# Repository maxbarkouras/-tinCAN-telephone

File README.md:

# tinCAN-telephone
Remotely send and receive CAN messages over WiFi.

**Hardware Requirements:**
- ESP32 (TWAI enabled)
- CAN Transceiver
  
**For OBD connections, you must also include:**
  - Buck Converter (minimum 12V at 1A)
  - OBD2 Cable

Wiring example using ESP32 Wroom, SN65HVD230, and LM2596:

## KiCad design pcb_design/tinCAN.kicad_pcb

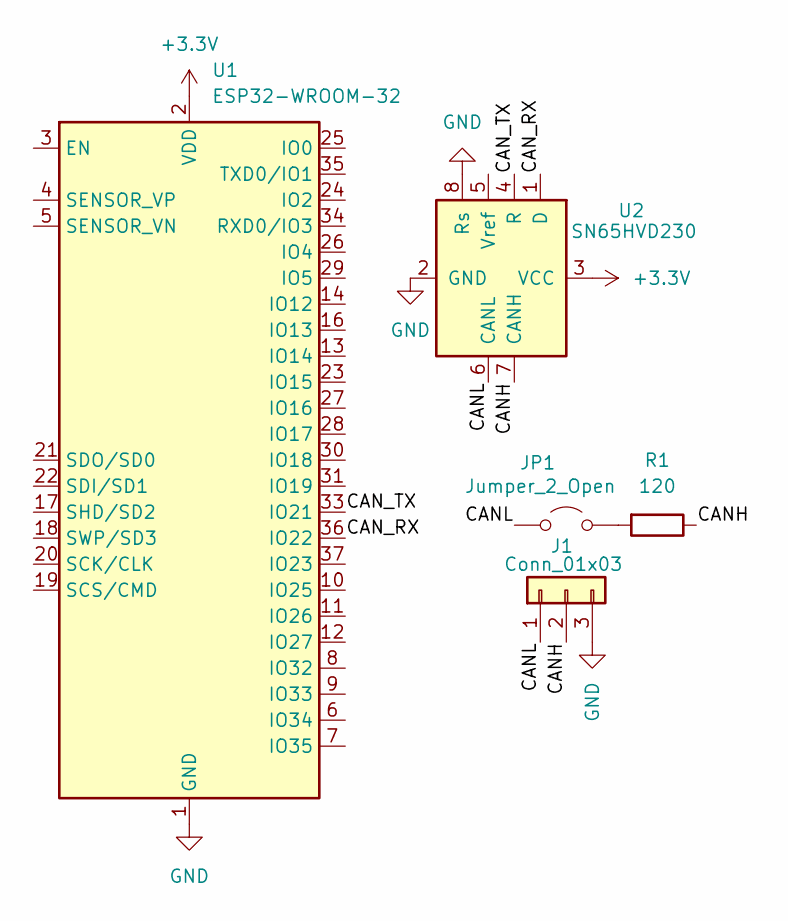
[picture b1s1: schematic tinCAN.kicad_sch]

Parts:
J1: Conn_01x03; PinSocket_1x03_P2.54mm_Vertical
JP1: Jumper_2_Open; PinSocket_1x02_P2.54mm_Vertical
R1: 120; R_0201_0603Metric
U1: ESP32-WROOM-32
U2: SN65HVD230; SOIC-8_3.9x4.9mm_P1.27mm

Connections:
+3.3V: U1.2 (VDD), U2.3 (VCC)
/CANH: J1.2, R1.1, U2.7 (CANH)
/CANL: J1.1, JP1.1 (A), U2.6 (CANL)
/CAN_RX: U1.36 (IO22), U2.1 (D)
/CAN_TX: U1.33 (IO21), U2.4 (R)
GND: J1.3, U1.1 (GND), U1.15 (GND), U1.38 (GND), U1.39 (GND), U2.2 (GND), U2.8 (Rs)
unnamed: JP1.2 (B), R1.2

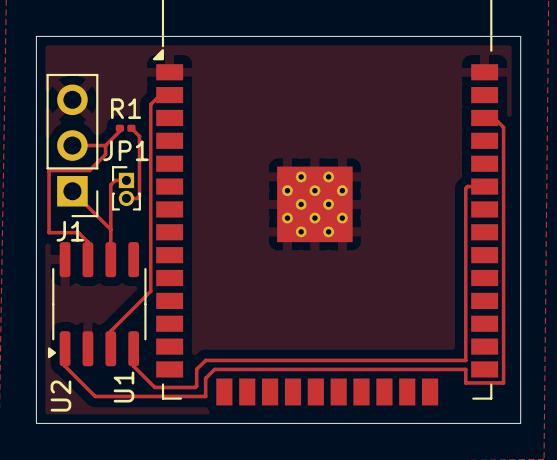
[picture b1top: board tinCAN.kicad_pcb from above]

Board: 2 copper layers, 26.9 x 21.5 mm, 5 parts (0 on the bottom side), 7 nets.

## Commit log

2025-09-07 Create tmp
